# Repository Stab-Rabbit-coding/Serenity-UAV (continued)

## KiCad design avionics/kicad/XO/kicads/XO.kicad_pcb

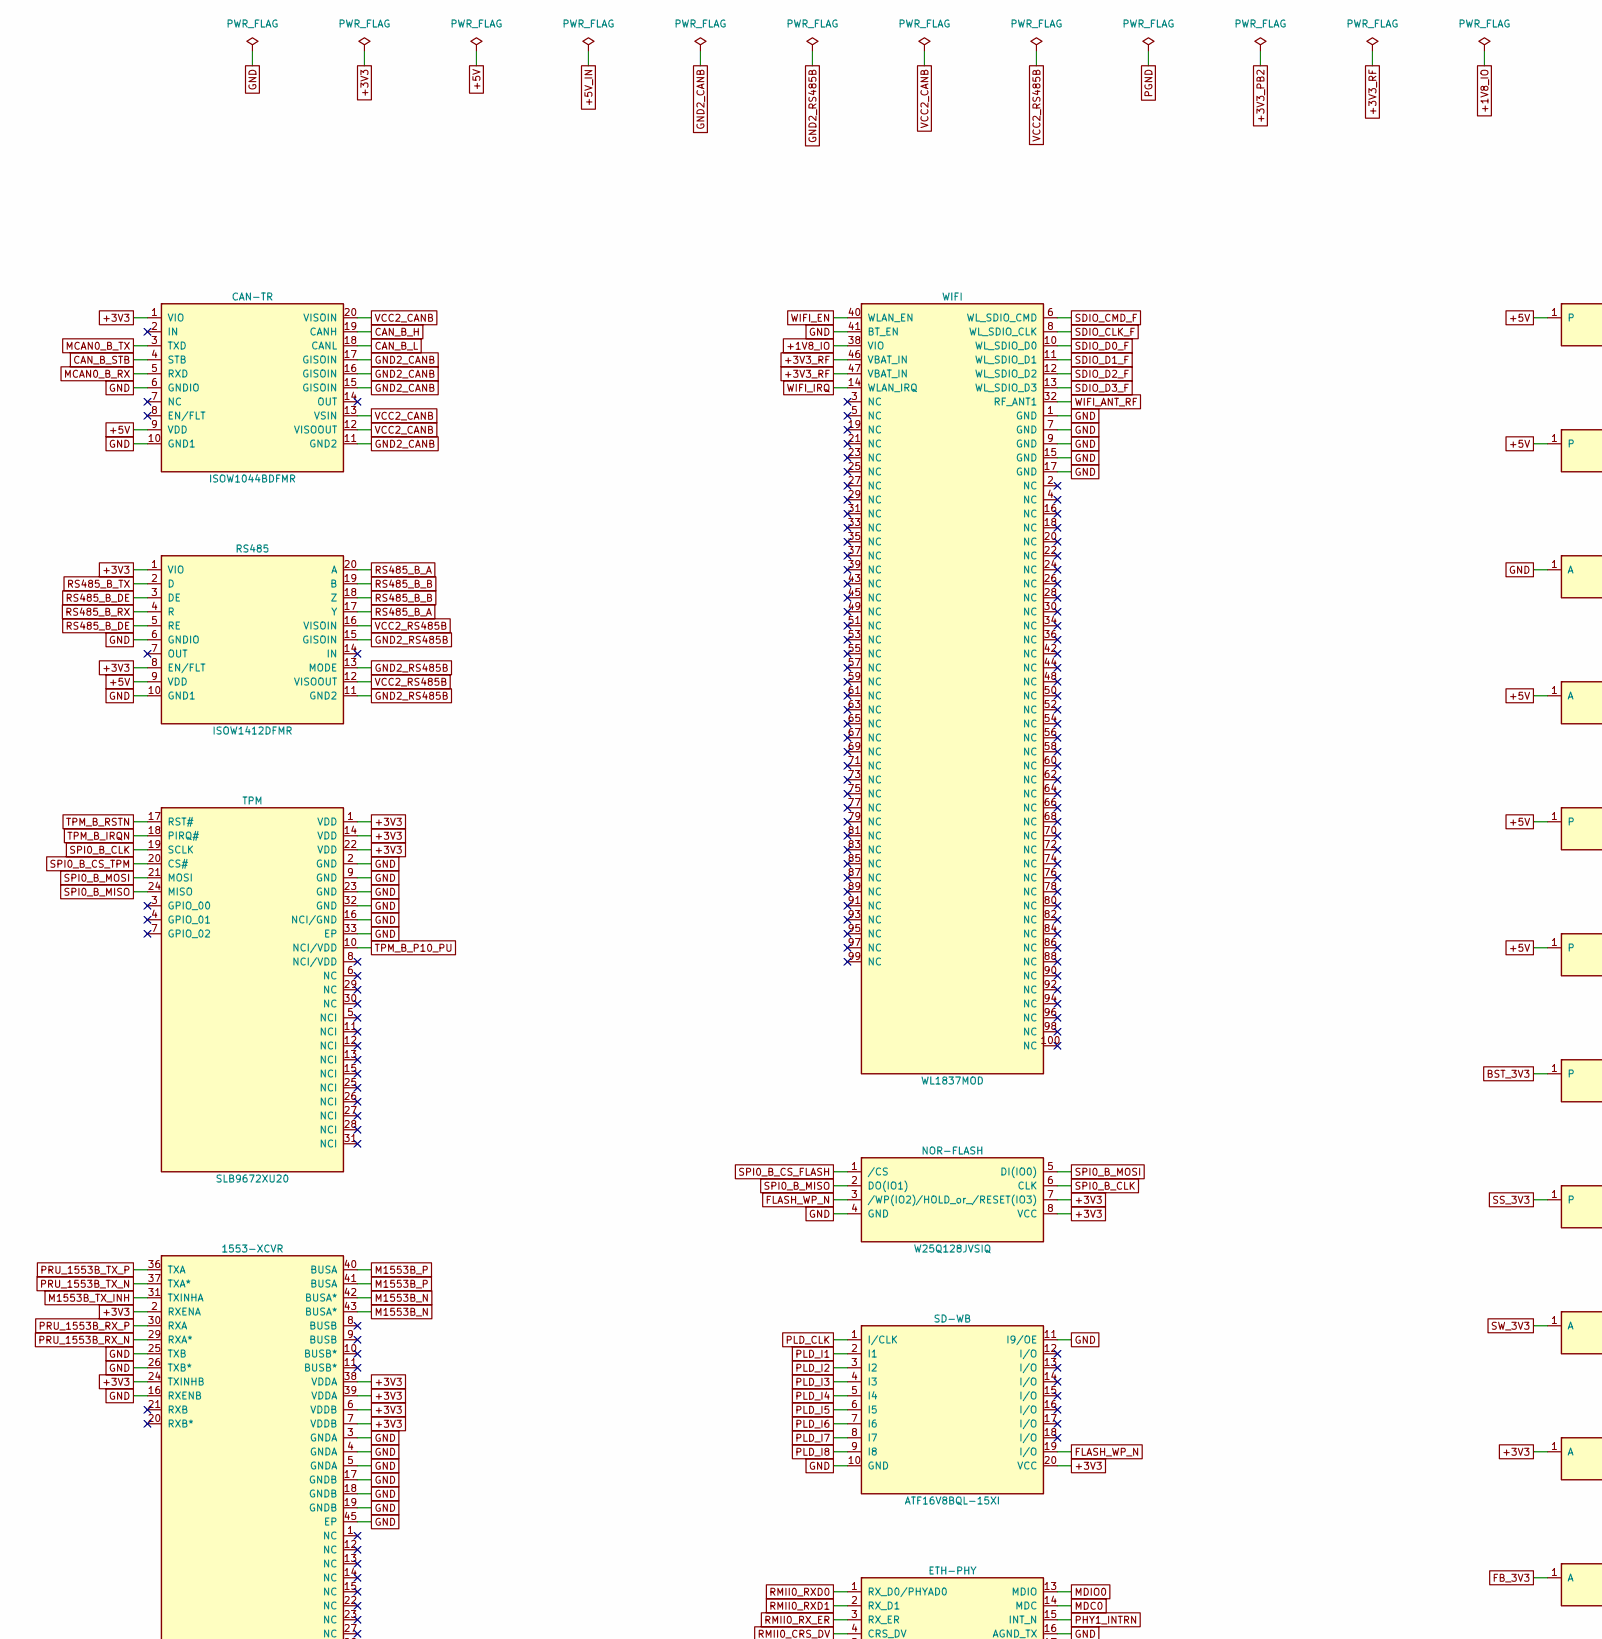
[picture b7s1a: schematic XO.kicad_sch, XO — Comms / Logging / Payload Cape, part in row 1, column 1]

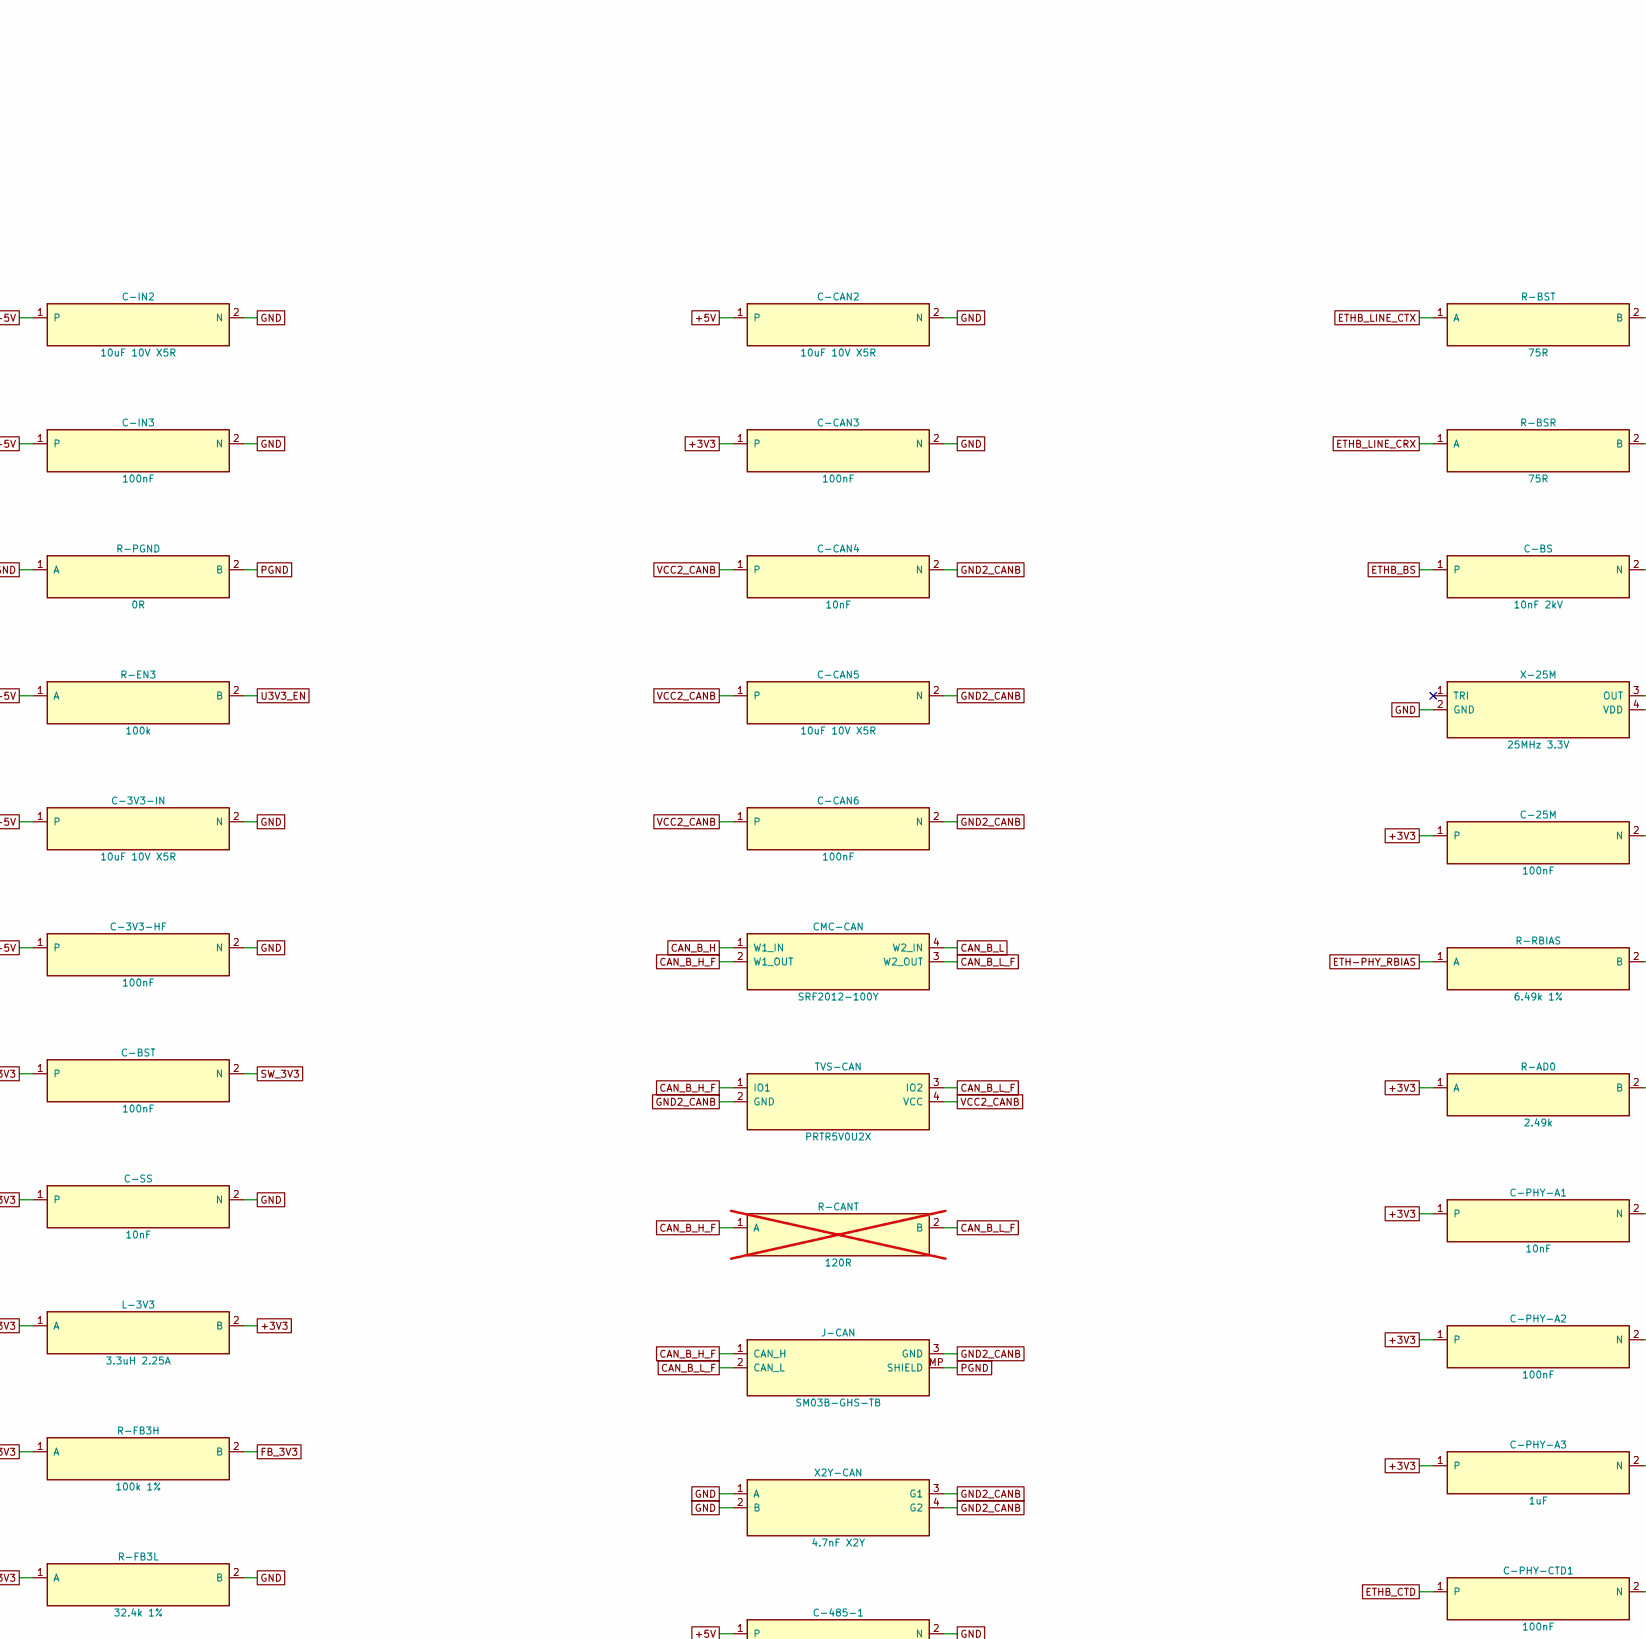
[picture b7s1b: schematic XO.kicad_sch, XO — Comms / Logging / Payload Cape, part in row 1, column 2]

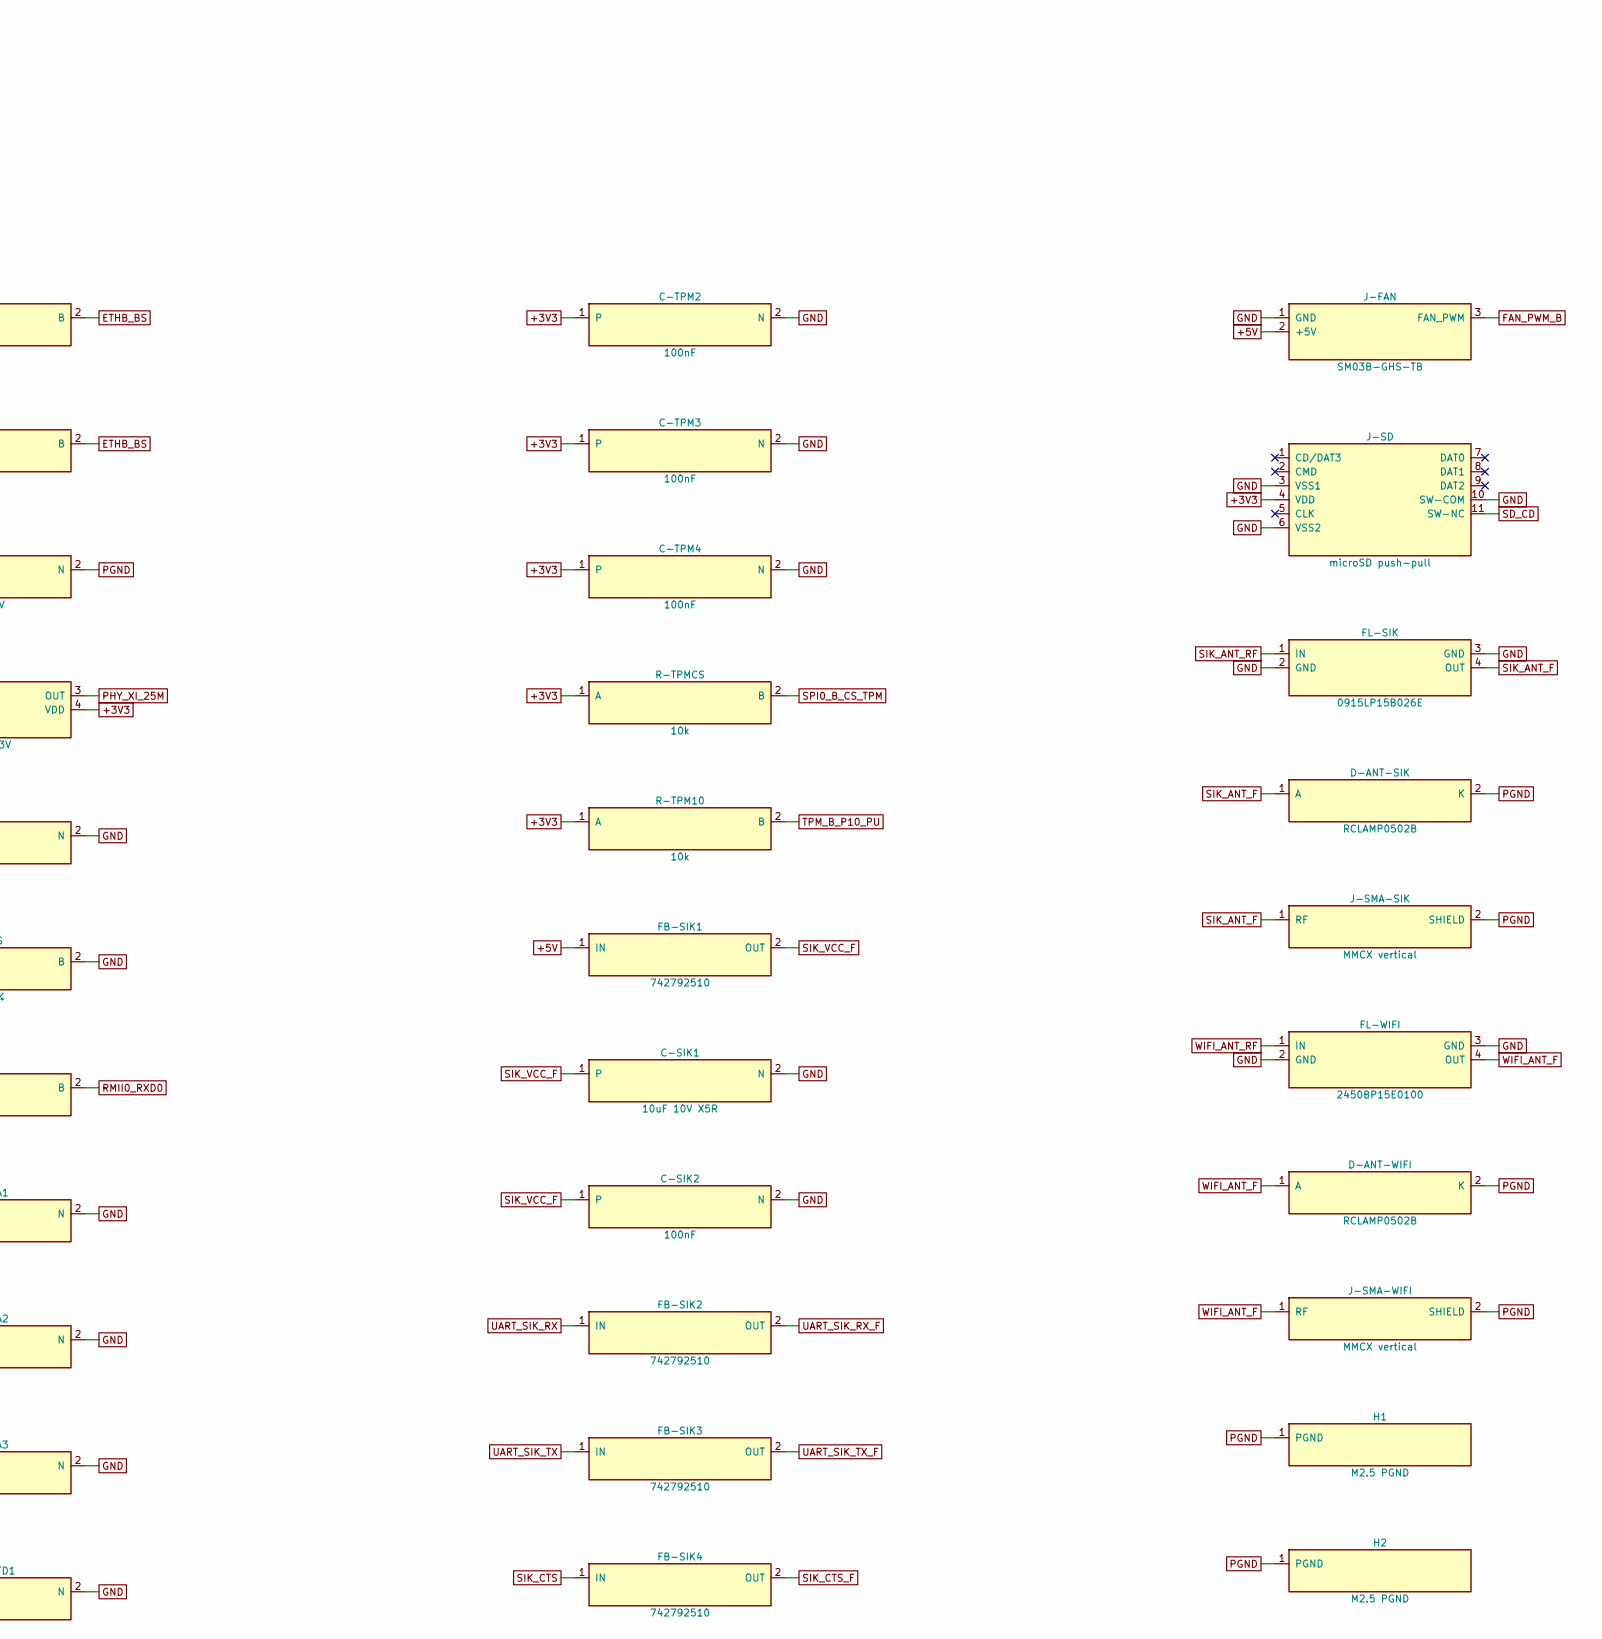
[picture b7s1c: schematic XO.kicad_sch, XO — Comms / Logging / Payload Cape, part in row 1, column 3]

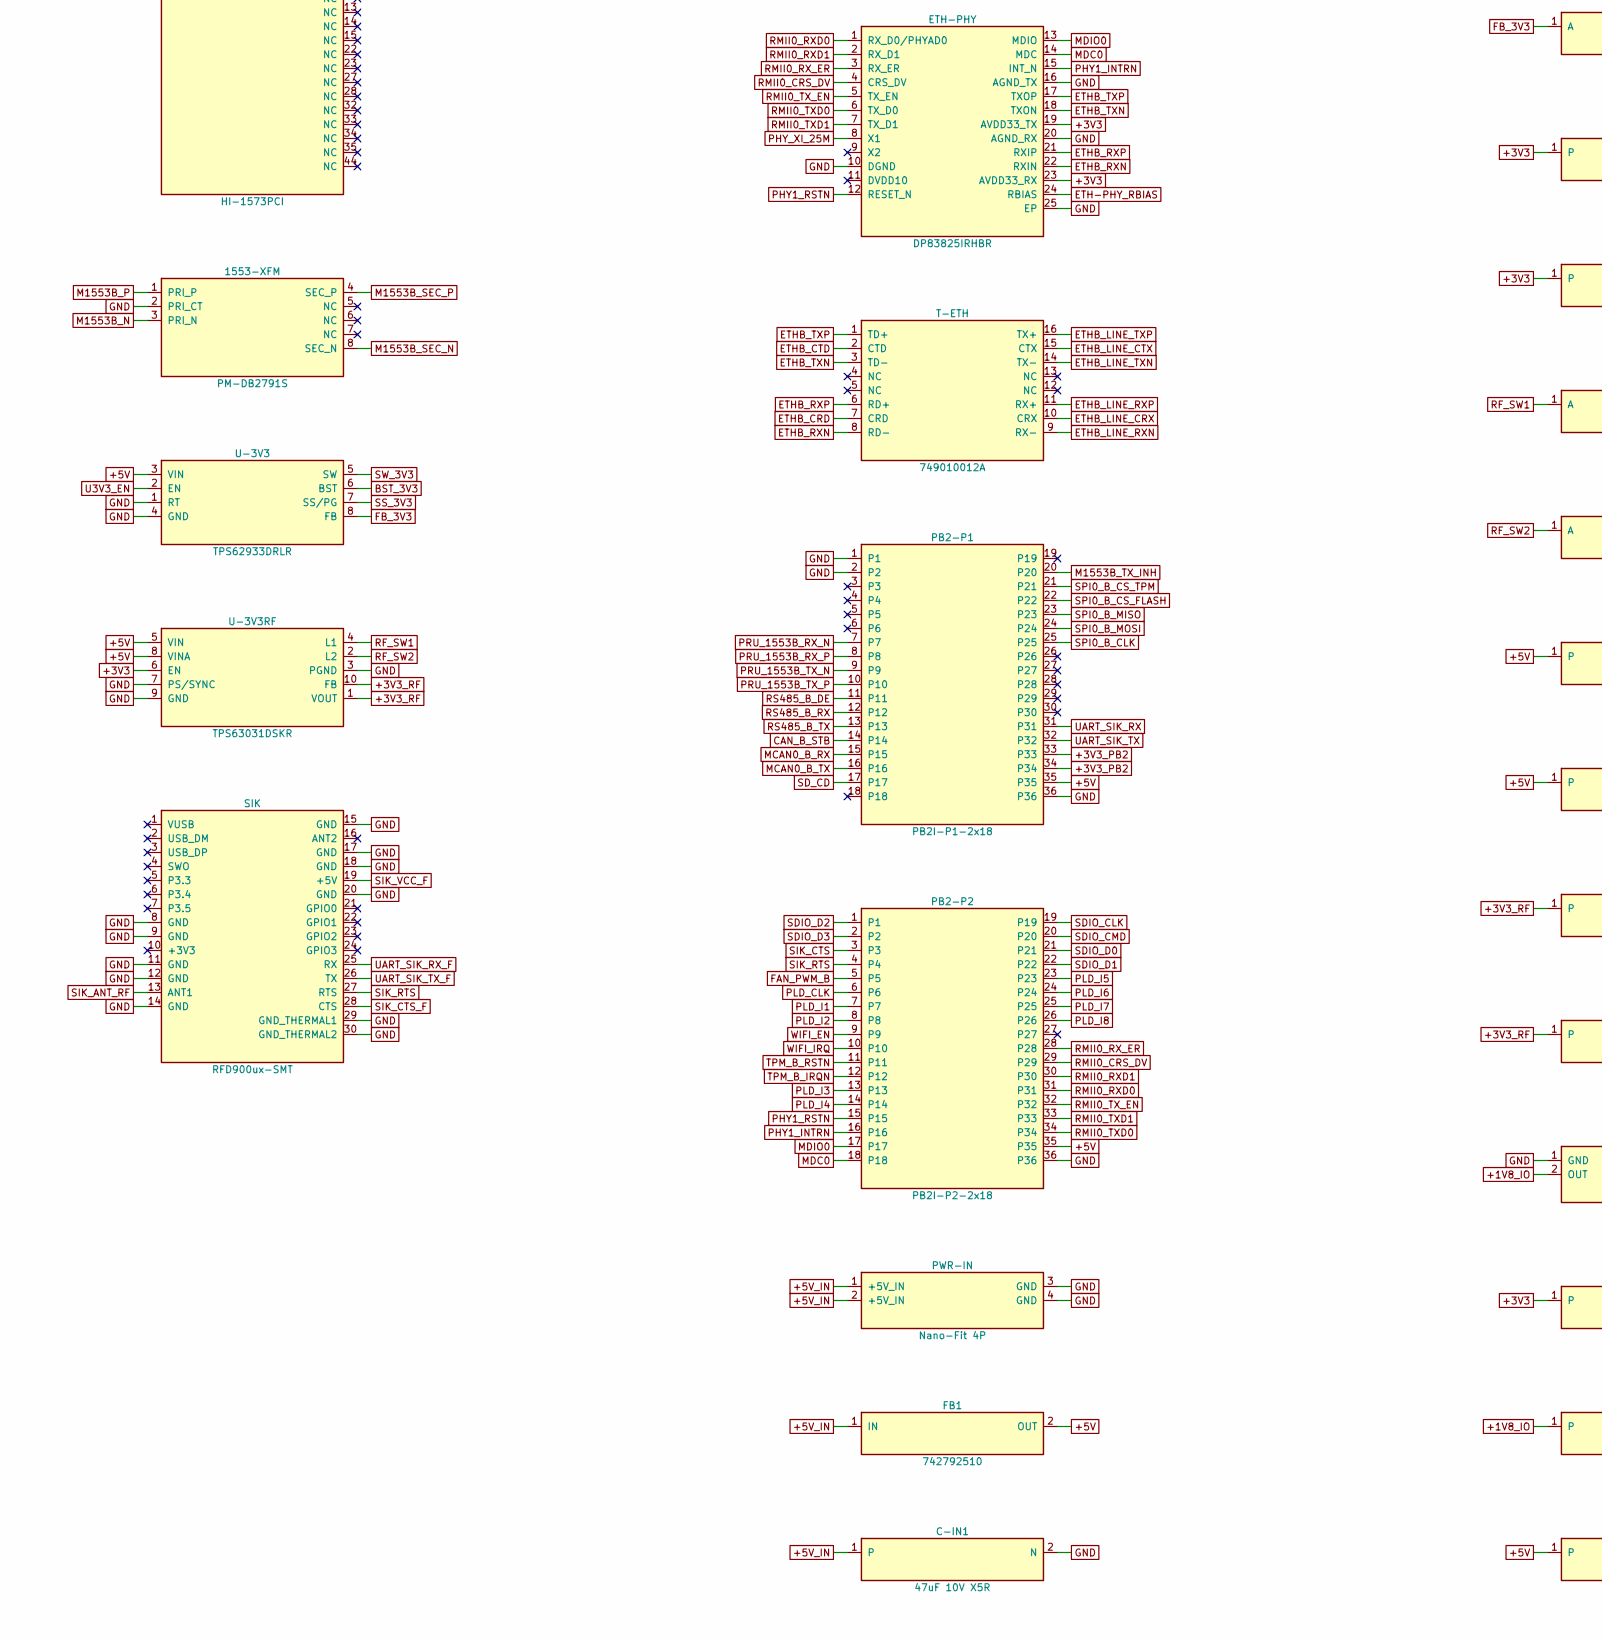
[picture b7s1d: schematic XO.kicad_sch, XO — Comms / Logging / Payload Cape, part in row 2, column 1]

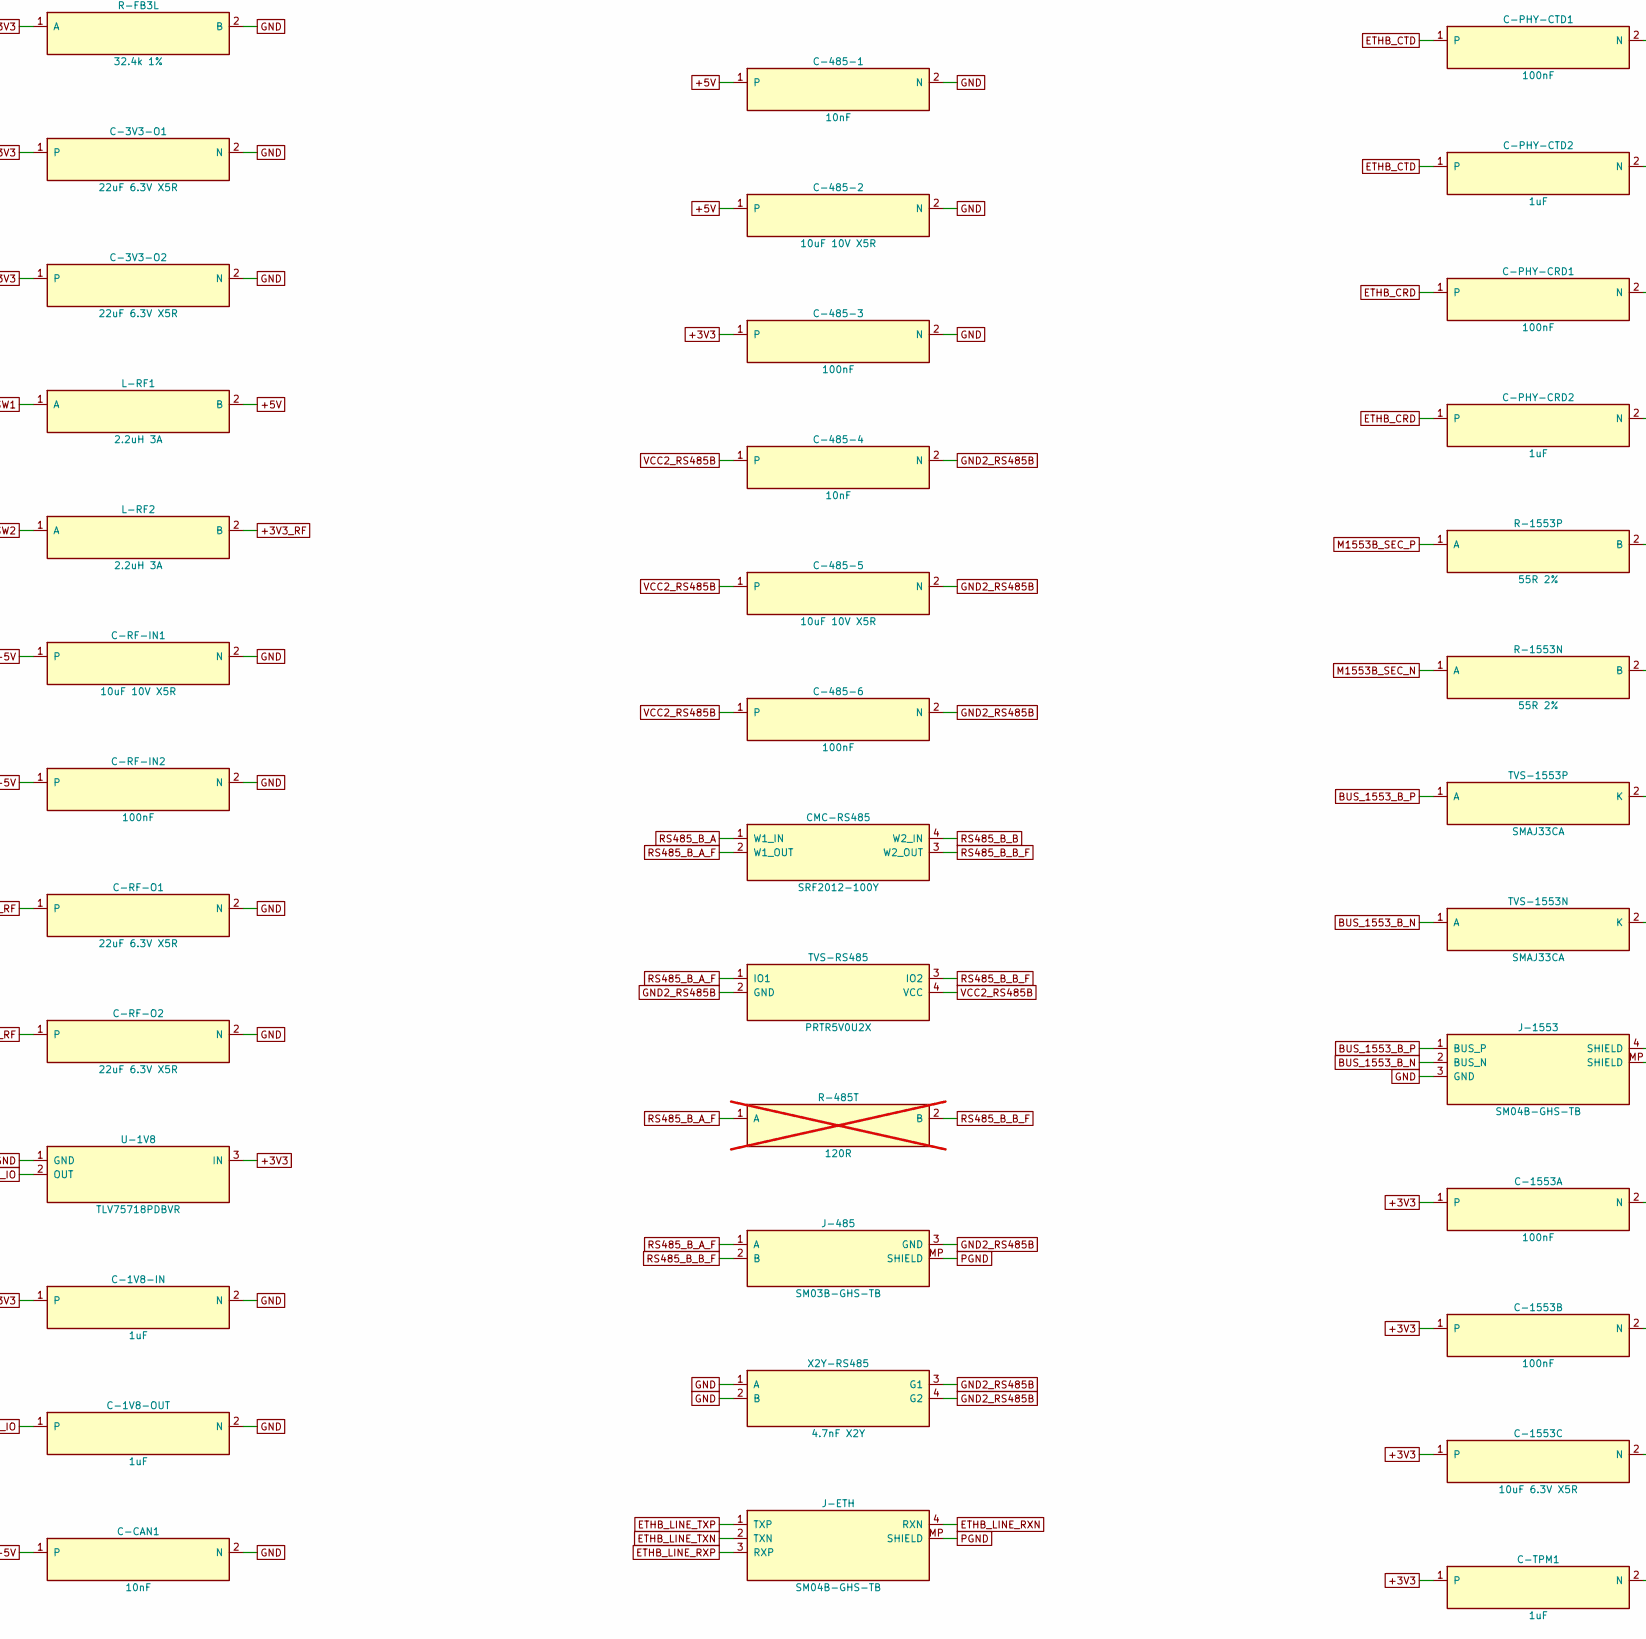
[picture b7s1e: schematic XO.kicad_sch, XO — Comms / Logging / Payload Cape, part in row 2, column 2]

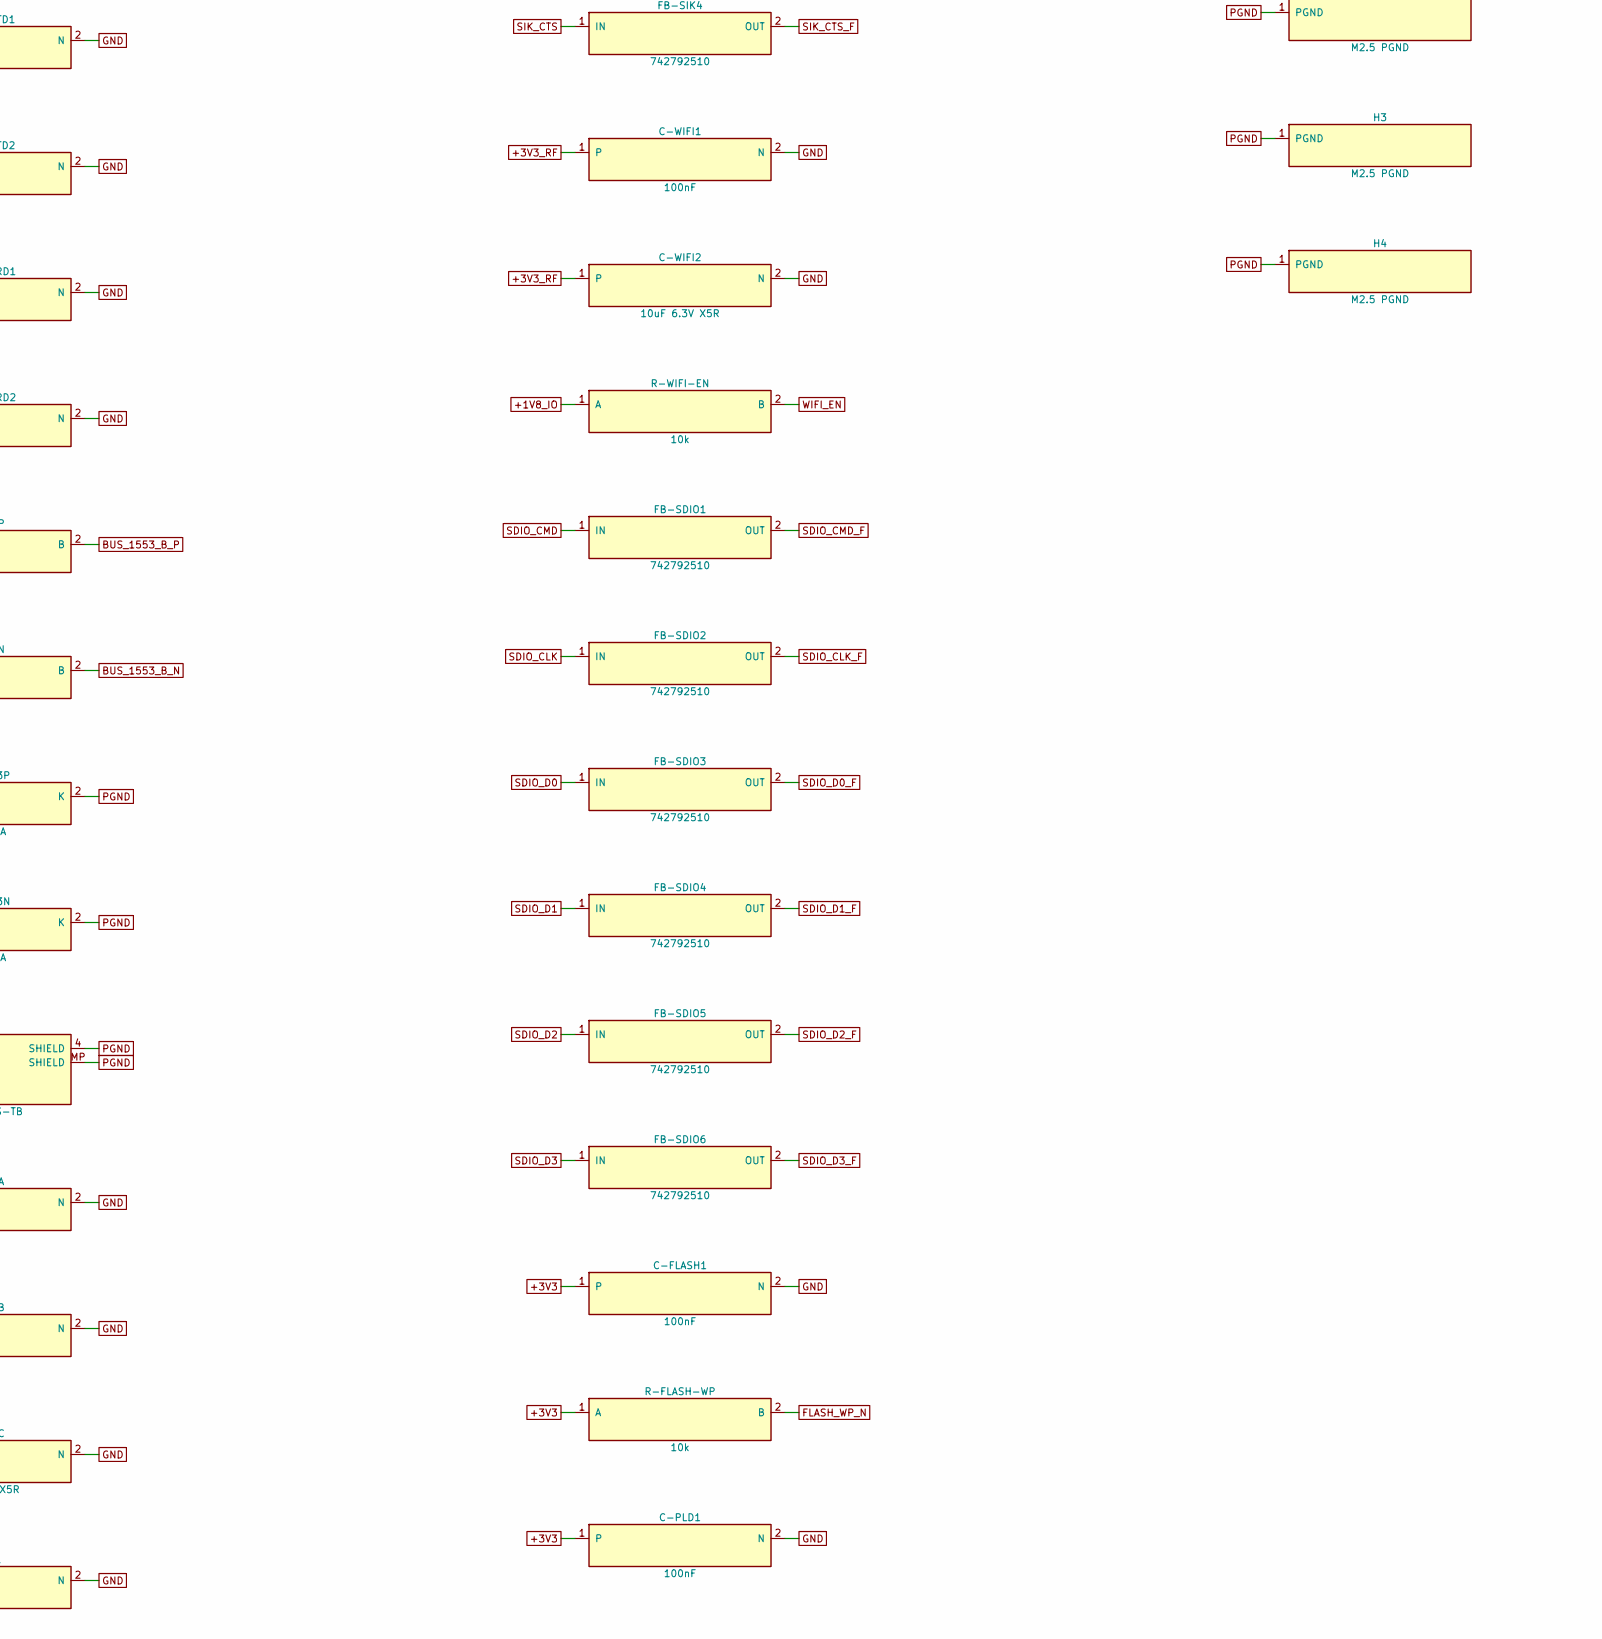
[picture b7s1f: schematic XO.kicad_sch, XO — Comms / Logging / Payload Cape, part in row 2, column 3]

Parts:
1553-XCVR: HI-1573PCI; QFN-44-1EP_7x7mm_P0.5mm_EP5.2x5.2mm; MPN HI-1573PCI
1553-XFM: PM-DB2791S; Xfmr_1553_SMD_0.40in_8pin; MPN PM-DB2791S
C-1V8-IN, C-1V8-OUT: 1uF; C_0402_1005Metric
C-3V3-HF, C-25M, C-485-3, C-485-6, C-1553A, C-1553B: 100nF; C_0402_1005Metric
C-3V3-IN, C-485-2, C-485-5: 10uF 10V X5R; C_0603_1608Metric
C-3V3-O1, C-3V3-O2: 22uF 6.3V X5R; C_0603_1608Metric
C-485-1, C-485-4: 10nF; C_0201_0603Metric
C-1553C: 10uF 6.3V X5R; C_0603_1608Metric
C-BS: 10nF 2kV; C_1808_4520Metric
C-BST: 100nF; C_0402_1005Metric
C-CAN1, C-CAN4: 10nF; C_0201_0603Metric
C-CAN2, C-CAN5: 10uF 10V X5R; C_0603_1608Metric
C-CAN3, C-CAN6: 100nF; C_0402_1005Metric
C-FLASH1: 100nF; C_0402_1005Metric
C-IN1: 47uF 10V X5R; C_1210_3225Metric
C-IN2: 10uF 10V X5R; C_0603_1608Metric
C-IN3: 100nF; C_0402_1005Metric
C-PHY-A1: 10nF; C_0201_0603Metric
C-PHY-A2: 100nF; C_0402_1005Metric
C-PHY-A3: 1uF; C_0402_1005Metric
C-PHY-CRD1: 100nF; C_0402_1005Metric
C-PHY-CRD2: 1uF; C_0402_1005Metric
C-PHY-CTD1: 100nF; C_0402_1005Metric
C-PHY-CTD2: 1uF; C_0402_1005Metric
C-PLD1: 100nF; C_0402_1005Metric
C-RF-IN1: 10uF 10V X5R; C_0603_1608Metric
C-RF-IN2: 100nF; C_0402_1005Metric
C-RF-O1, C-RF-O2: 22uF 6.3V X5R; C_0603_1608Metric
C-SIK1: 10uF 10V X5R; C_0603_1608Metric
C-SIK2: 100nF; C_0402_1005Metric
C-SS: 10nF; C_0201_0603Metric
C-TPM1: 1uF; C_0402_1005Metric
C-TPM2, C-TPM3, C-TPM4: 100nF; C_0402_1005Metric
C-WIFI1: 100nF; C_0402_1005Metric
C-WIFI2: 10uF 6.3V X5R; C_0603_1608Metric
CAN-TR: ISOW1044BDFMR; SOIC-20W_7.5x12.8mm_P1.27mm; MPN ISOW1044BDFMR
CMC-CAN: SRF2012-100Y; Bourns_SRF2012_4T; MPN SRF2012-121YA
CMC-RS485: SRF2012-100Y; Bourns_SRF2012_4T; MPN SRF2012-121YA
D-ANT-SIK: RCLAMP0502B; RCLAMP0502B_SOD882; MPN RCLAMP0502BTCL
D-ANT-WIFI: RCLAMP0502B; RCLAMP0502B_SOD882; MPN RCLAMP0502BTCL
ETH-PHY: DP83825IRHBR; Texas_RMQ0024A_WQFN-24-1EP_3x3mm_P0.4mm_EP1.9x1.9mm; MPN DP83825IRHBR
FB1: 742792510; L_1812_4532Metric; MPN 742792510
FB-SDIO1, FB-SDIO2, FB-SDIO3, FB-SDIO4, FB-SDIO5, FB-SDIO6: 742792510; L_1812_4532Metric; MPN 742792510
FB-SIK1, FB-SIK2, FB-SIK3, FB-SIK4: 742792510; L_1812_4532Metric; MPN 742792510
FL-SIK: 0915LP15B026E; Johanson_0915LP15B026E_SMD4; MPN 0915LP15B026E
FL-WIFI: 2450BP15E0100; Johanson_2450BP15E0100_SMD4; MPN 2450BP15E0100
H1, H2, H3, H4: M2.5 PGND; MountingHole_2.7mm_M2.5_PGND_Ring
J-485: SM03B-GHS-TB; JST_GH_SM03B-GHS-TB_1x03-1MP_P1.25mm_Horizontal; MPN SM03B-GHS-TB(LF)(SN)
J-1553: SM04B-GHS-TB; JST_GH_SM04B-GHS-TB_1x04-1MP_P1.25mm_Horizontal; MPN SM04B-GHS-TB(LF)(SN)
J-CAN: SM03B-GHS-TB; JST_GH_SM03B-GHS-TB_1x03-1MP_P1.25mm_Horizontal; MPN SM03B-GHS-TB(LF)(SN)
J-ETH: SM04B-GHS-TB; JST_GH_SM04B-GHS-TB_1x04-1MP_P1.25mm_Horizontal; MPN SM04B-GHS-TB(LF)(SN)
J-FAN: SM03B-GHS-TB; JST_GH_SM03B-GHS-TB_1x03-1MP_P1.25mm_Horizontal; MPN SM03B-GHS-TB(LF)(SN)
J-SD: microSD push-pull; microSD_HC_Molex_104031-0811; MPN 104031-0811
J-SMA-SIK: MMCX vertical; MMCX_Molex_73415-1471_Vertical; MPN 73415-1471
J-SMA-WIFI: MMCX vertical; MMCX_Molex_73415-1471_Vertical; MPN 73415-1471
L-3V3: 3.3uH 2.25A; L_WE-MAPI_3015; MPN 74438335033
L-RF1, L-RF2: 2.2uH 3A; L_Wuerth_MAPI-3015; MPN LPS3015-222MRC
NOR-FLASH: W25Q128JVSIQ; SOIC-8_3.9x4.9mm_P1.27mm; MPN W25Q128JVSIQ
PB2-P1: PB2I-P1-2x18; PocketBeagle2_2x18_P1_Socket
PB2-P2: PB2I-P2-2x18; PocketBeagle2_2x18_P2_Socket
PWR-IN: Nano-Fit 4P; Molex_NanoFit_1x04_Horizontal; MPN 105313-1204
R-485T: 120R; R_0402_1005Metric; not fitted
R-1553N, R-1553P: 55R 2%; R_0603_1608Metric
R-AD0: 2.49k; R_0201_0603Metric
R-BSR: 75R; R_0402_1005Metric
R-BST: 75R; R_0402_1005Metric
R-CANT: 120R; R_0402_1005Metric; not fitted
R-EN3: 100k; R_0201_0603Metric
R-FB3H: 100k 1%; R_0201_0603Metric
R-FB3L: 32.4k 1%; R_0201_0603Metric
R-FLASH-WP: 10k; R_0201_0603Metric
R-PGND: 0R; R_0805_2012Metric
R-RBIAS: 6.49k 1%; R_0201_0603Metric
R-TPM10: 10k; R_0201_0603Metric
R-TPMCS: 10k; R_0201_0603Metric
R-WIFI-EN: 10k; R_0201_0603Metric
RS485: ISOW1412DFMR; SOIC-20W_7.5x12.8mm_P1.27mm; MPN ISOW1412DFMR
SD-WB: ATF16V8BQL-15XI; TSSOP-20_4.4x6.5mm_P0.65mm; MPN ATF16V8BQL-15XI
SIK: RFD900ux-SMT; RFDesign_RFD900ux_SMT; MPN RFD900UX-SMT
T-ETH: 749010012A; Wurth_749010012A_WE-LAN; MPN 749010012A
TPM: SLB9672XU20; QFN-32-1EP_5x5mm_P0.5mm_EP3.6x3.6mm; MPN SLB9672XU20FW1611XUMA1
TVS-1553N, TVS-1553P: SMAJ33CA; D_SMA; MPN SMAJ33CA
TVS-CAN: PRTR5V0U2X; SOT-143; MPN PRTR5V0U2X,315
TVS-RS485: PRTR5V0U2X; SOT-143; MPN PRTR5V0U2X,315
U-1V8: TLV75718PDBVR; SOT-89-3; MPN TLV75718PDBVR
U-3V3: TPS62933DRLR; SOT-583-8; MPN TPS62933DRLR
U-3V3RF: TPS63031DSKR; TPS6303x_VSON-10_2p5; MPN TPS63031DSKR
WIFI: WL1837MOD; WL1837MOD_MOC_100; MPN WL1837MOD
X2Y-CAN, X2Y-RS485: 4.7nF X2Y; X2Y_0805_4T; MPN CX0805MRX7R0BB472
X-25M: 25MHz 3.3V; Oscillator_SMD_ECS_2520MV-xxx-xx-4Pin_2.5x2.0mm; MPN ECS-2520MV-250-BN-TR

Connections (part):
+1V8_IO: C-1V8-OUT.1, R-WIFI-EN.1 (A), U-1V8.2 (OUT), WIFI.38 (VIO)
+3V3: 1553-XCVR.2 (RXENA), 1553-XCVR.6 (VDDB), 1553-XCVR.7 (VDDB), 1553-XCVR.24 (TXINHB), 1553-XCVR.38 (VDDA), 1553-XCVR.39 (VDDA), C-1V8-IN.1, C-3V3-O1.1, C-3V3-O2.1, C-25M.1, C-485-3.1, C-1553A.1, C-1553B.1, C-1553C.1, C-CAN3.1, C-FLASH1.1, C-PHY-A1.1, C-PHY-A2.1, C-PHY-A3.1, C-PLD1.1, C-TPM1.1, C-TPM2.1, C-TPM3.1, C-TPM4.1, CAN-TR.1 (VIO), ETH-PHY.19 (AVDD33_TX), ETH-PHY.23 (AVDD33_RX), J-SD.4 (VDD), L-3V3.2 (B), NOR-FLASH.7 (/HOLD_or_/RESET(IO3)), NOR-FLASH.8 (VCC), R-AD0.1 (A), R-FB3H.1 (A), R-FLASH-WP.1 (A), R-TPM10.1 (A), R-TPMCS.1 (A), RS485.1 (VIO), RS485.8 (EN/FLT), SD-WB.20 (VCC), TPM.1 (VDD), TPM.14 (VDD), TPM.22 (VDD), U-1V8.3 (IN), U-3V3RF.6 (EN), X-25M.4 (VDD)
+3V3_PB2: PB2-P1.33, PB2-P1.34
+3V3_RF: C-RF-O1.1, C-RF-O2.1, C-WIFI1.1, C-WIFI2.1, L-RF2.2 (B), U-3V3RF.1 (VOUT), U-3V3RF.10 (FB), WIFI.46 (VBAT_IN), WIFI.47 (VBAT_IN)
+5V: C-3V3-HF.1, C-3V3-IN.1, C-485-1.1, C-485-2.1, C-CAN1.1, C-CAN2.1, C-IN2.1, C-IN3.1, C-RF-IN1.1, C-RF-IN2.1, CAN-TR.9 (VDD), FB1.2 (OUT), FB-SIK1.1 (IN), J-FAN.2 (+5V), L-RF1.2 (B), PB2-P1.35, PB2-P2.35, R-EN3.1 (A), RS485.9 (VDD), U-3V3.3 (VIN), U-3V3RF.5 (VIN), U-3V3RF.8 (VINA)
+5V_IN: C-IN1.1, FB1.1 (IN), PWR-IN.1 (+5V_IN), PWR-IN.2 (+5V_IN)
BST_3V3: C-BST.1, U-3V3.6 (BST)
BUS_1553_B_N: J-1553.2 (BUS_N), R-1553N.2 (B), TVS-1553N.1 (A)
BUS_1553_B_P: J-1553.1 (BUS_P), R-1553P.2 (B), TVS-1553P.1 (A)
CAN_B_H: CAN-TR.19 (CANH), CMC-CAN.1 (W1_IN)
CAN_B_H_F: CMC-CAN.2 (W1_OUT), J-CAN.1 (CAN_H), R-CANT.1 (A), TVS-CAN.1 (IO1)
CAN_B_L: CAN-TR.18 (CANL), CMC-CAN.4 (W2_IN)
CAN_B_L_F: CMC-CAN.3 (W2_OUT), J-CAN.2 (CAN_L), R-CANT.2 (B), TVS-CAN.3 (IO2)
CAN_B_STB: CAN-TR.4 (STB), PB2-P1.14
ETH-PHY_RBIAS: ETH-PHY.24 (RBIAS), R-RBIAS.1 (A)
ETHB_BS: C-BS.1, R-BSR.2 (B), R-BST.2 (B)
ETHB_CRD: C-PHY-CRD1.1, C-PHY-CRD2.1, T-ETH.7 (CRD)
ETHB_CTD: C-PHY-CTD1.1, C-PHY-CTD2.1, T-ETH.2 (CTD)
ETHB_LINE_CRX: R-BSR.1 (A), T-ETH.10 (CRX)
ETHB_LINE_CTX: R-BST.1 (A), T-ETH.15 (CTX)
ETHB_LINE_RXN: J-ETH.4 (RXN), T-ETH.9 (RX-)
ETHB_LINE_RXP: J-ETH.3 (RXP), T-ETH.11 (RX+)
ETHB_LINE_TXN: J-ETH.2 (TXN), T-ETH.14 (TX-)
ETHB_LINE_TXP: J-ETH.1 (TXP), T-ETH.16 (TX+)
ETHB_RXN: ETH-PHY.22 (RXIN), T-ETH.8 (RD-)
ETHB_RXP: ETH-PHY.21 (RXIP), T-ETH.6 (RD+)
ETHB_TXN: ETH-PHY.18 (TXON), T-ETH.3 (TD-)
ETHB_TXP: ETH-PHY.17 (TXOP), T-ETH.1 (TD+)
FAN_PWM_B: J-FAN.3 (FAN_PWM), PB2-P2.5
FB_3V3: R-FB3H.2 (B), R-FB3L.1 (A), U-3V3.8 (FB)
FLASH_WP_N: NOR-FLASH.3 (/WP(IO2)), R-FLASH-WP.2 (B), SD-WB.19 (I/O)
GND: 1553-XCVR.3 (GNDA), 1553-XCVR.4 (GNDA), 1553-XCVR.5 (GNDA), 1553-XCVR.16 (RXENB), 1553-XCVR.17 (GNDB), 1553-XCVR.18 (GNDB), 1553-XCVR.19 (GNDB), 1553-XCVR.25 (TXB), 1553-XCVR.26 (TXB*), 1553-XCVR.45 (EP), 1553-XFM.2 (PRI_CT), C-1V8-IN.2 (N), C-1V8-OUT.2 (N), C-3V3-HF.2 (N), C-3V3-IN.2 (N), C-3V3-O1.2 (N), C-3V3-O2.2 (N), C-25M.2 (N), C-485-1.2 (N), C-485-2.2 (N), C-485-3.2 (N), C-1553A.2 (N), C-1553B.2 (N), C-1553C.2 (N), C-CAN1.2 (N), C-CAN2.2 (N), C-CAN3.2 (N), C-FLASH1.2 (N), C-IN1.2 (N), C-IN2.2 (N), C-IN3.2 (N), C-PHY-A1.2 (N), C-PHY-A2.2 (N), C-PHY-A3.2 (N), C-PHY-CRD1.2 (N), C-PHY-CRD2.2 (N), C-PHY-CTD1.2 (N), C-PHY-CTD2.2 (N), C-PLD1.2 (N), C-RF-IN1.2 (N), C-RF-IN2.2 (N), C-RF-O1.2 (N), C-RF-O2.2 (N), C-SIK1.2 (N), C-SIK2.2 (N), C-SS.2 (N), C-TPM1.2 (N), C-TPM2.2 (N), C-TPM3.2 (N), C-TPM4.2 (N), C-WIFI1.2 (N), C-WIFI2.2 (N), CAN-TR.6 (GNDIO), CAN-TR.10 (GND1), ETH-PHY.10 (DGND), ETH-PHY.16 (AGND_TX), ETH-PHY.20 (AGND_RX), ETH-PHY.25 (EP), FL-SIK.2 (GND), FL-SIK.3 (GND), FL-WIFI.2 (GND), FL-WIFI.3 (GND), J-1553.3 (GND), J-FAN.1 (GND), J-SD.3 (VSS1), J-SD.6 (VSS2), J-SD.10 (SW-COM), NOR-FLASH.4 (GND), PB2-P1.1, PB2-P1.2, PB2-P1.36, PB2-P2.36, PWR-IN.3 (GND), PWR-IN.4 (GND), R-FB3L.2 (B), R-PGND.1 (A), R-RBIAS.2 (B), RS485.6 (GNDIO), RS485.10 (GND1), SD-WB.10 (GND)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
GND2_CANB: C-CAN4.2 (N), C-CAN5.2 (N), C-CAN6.2 (N), CAN-TR.11 (GND2), CAN-TR.15 (GISOIN), CAN-TR.16 (GISOIN), CAN-TR.17 (GISOIN), J-CAN.3 (GND), TVS-CAN.2 (GND), X2Y-CAN.3 (G1), X2Y-CAN.4 (G2)
GND2_RS485B: C-485-4.2 (N), C-485-5.2 (N), C-485-6.2 (N), J-485.3 (GND), RS485.11 (GND2), RS485.13 (MODE), RS485.15 (GISOIN), TVS-RS485.2 (GND), X2Y-RS485.3 (G1), X2Y-RS485.4 (G2)
M1553B_N: 1553-XCVR.42 (BUSA*), 1553-XCVR.43 (BUSA*), 1553-XFM.3 (PRI_N)
M1553B_P: 1553-XCVR.40 (BUSA), 1553-XCVR.41 (BUSA), 1553-XFM.1 (PRI_P)
M1553B_SEC_N: 1553-XFM.8 (SEC_N), R-1553N.1 (A)
M1553B_SEC_P: 1553-XFM.4 (SEC_P), R-1553P.1 (A)
M1553B_TX_INH: 1553-XCVR.31 (TXINHA), PB2-P1.20
MCAN0_B_RX: CAN-TR.5 (RXD), PB2-P1.15
MCAN0_B_TX: CAN-TR.3 (TXD), PB2-P1.16
MDC0: ETH-PHY.14 (MDC), PB2-P2.18
MDIO0: ETH-PHY.13 (MDIO), PB2-P2.17
PGND: C-BS.2 (N), D-ANT-SIK.2 (K), D-ANT-WIFI.2 (K), H1.1, H2.1, H3.1, H4.1, J-485.MP (SHIELD), J-1553.4 (SHIELD), J-1553.MP (SHIELD), J-CAN.MP (SHIELD), J-ETH.MP (SHIELD), J-SMA-SIK.2 (SHIELD), J-SMA-WIFI.2 (SHIELD), R-PGND.2 (B), TVS-1553N.2 (K), TVS-1553P.2 (K)
PHY1_INTRN: ETH-PHY.15 (INT_N), PB2-P2.16
PHY1_RSTN: ETH-PHY.12 (RESET_N), PB2-P2.15
PHY_XI_25M: ETH-PHY.8 (X1), X-25M.3 (OUT)
PLD_CLK: PB2-P2.6, SD-WB.1 (I/CLK)
PLD_I1: PB2-P2.7, SD-WB.2 (I1)
PLD_I2: PB2-P2.8, SD-WB.3 (I2)
PLD_I3: PB2-P2.13, SD-WB.4 (I3)
PLD_I4: PB2-P2.14, SD-WB.5 (I4)
PLD_I5: PB2-P2.23, SD-WB.6 (I5)
PLD_I6: PB2-P2.24, SD-WB.7 (I6)
PLD_I7: PB2-P2.25, SD-WB.8 (I7)
PLD_I8: PB2-P2.26, SD-WB.9 (I8)
PRU_1553B_RX_N: 1553-XCVR.29 (RXA*), PB2-P1.7
PRU_1553B_RX_P: 1553-XCVR.30 (RXA), PB2-P1.8
PRU_1553B_TX_N: 1553-XCVR.37 (TXA*), PB2-P1.9
PRU_1553B_TX_P: 1553-XCVR.36 (TXA), PB2-P1.10
RF_SW1: L-RF1.1 (A), U-3V3RF.4 (L1)
RF_SW2: L-RF2.1 (A), U-3V3RF.2 (L2)
RMII0_CRS_DV: ETH-PHY.4 (CRS_DV), PB2-P2.29
RMII0_RXD0: ETH-PHY.1 (RX_D0/PHYAD0), PB2-P2.31, R-AD0.2 (B)
RMII0_RXD1: ETH-PHY.2 (RX_D1), PB2-P2.30
RMII0_RX_ER: ETH-PHY.3 (RX_ER), PB2-P2.28
RMII0_TXD0: ETH-PHY.6 (TX_D0), PB2-P2.34
RMII0_TXD1: ETH-PHY.7 (TX_D1), PB2-P2.33
RMII0_TX_EN: ETH-PHY.5 (TX_EN), PB2-P2.32
RS485_B_A: CMC-RS485.1 (W1_IN), RS485.17 (Y), RS485.20 (A)
RS485_B_A_F: CMC-RS485.2 (W1_OUT), J-485.1 (A), R-485T.1 (A), TVS-RS485.1 (IO1)
RS485_B_B: CMC-RS485.4 (W2_IN), RS485.18 (Z), RS485.19 (B)
RS485_B_B_F: CMC-RS485.3 (W2_OUT), J-485.2 (B), R-485T.2 (B), TVS-RS485.3 (IO2)
RS485_B_DE: PB2-P1.11, RS485.3 (DE), RS485.5 (RE)
RS485_B_RX: PB2-P1.12, RS485.4 (R)
RS485_B_TX: PB2-P1.13, RS485.2 (D)
SDIO_CLK: FB-SDIO2.1 (IN), PB2-P2.19
SDIO_CLK_F: FB-SDIO2.2 (OUT), WIFI.8 (WL_SDIO_CLK)
SDIO_CMD: FB-SDIO1.1 (IN), PB2-P2.20
SDIO_CMD_F: FB-SDIO1.2 (OUT), WIFI.6 (WL_SDIO_CMD)
SDIO_D0: FB-SDIO3.1 (IN), PB2-P2.21
SDIO_D0_F: FB-SDIO3.2 (OUT), WIFI.10 (WL_SDIO_D0)
SDIO_D1: FB-SDIO4.1 (IN), PB2-P2.22
SDIO_D1_F: FB-SDIO4.2 (OUT), WIFI.11 (WL_SDIO_D1)
SDIO_D2: FB-SDIO5.1 (IN), PB2-P2.1
SDIO_D2_F: FB-SDIO5.2 (OUT), WIFI.12 (WL_SDIO_D2)
SDIO_D3: FB-SDIO6.1 (IN), PB2-P2.2
SDIO_D3_F: FB-SDIO6.2 (OUT), WIFI.13 (WL_SDIO_D3)
SD_CD: J-SD.11 (SW-NC), PB2-P1.17
SIK_ANT_F: D-ANT-SIK.1 (A), FL-SIK.4 (OUT), J-SMA-SIK.1 (RF)
SIK_ANT_RF: FL-SIK.1 (IN), SIK.13 (ANT1)
SIK_CTS: FB-SIK4.1 (IN), PB2-P2.3
SIK_CTS_F: FB-SIK4.2 (OUT), SIK.28 (CTS)
SIK_RTS: PB2-P2.4, SIK.27 (RTS)
SIK_VCC_F: C-SIK1.1, C-SIK2.1, FB-SIK1.2 (OUT), SIK.19 (+5V)
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
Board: 6 copper layers, 121 parts (40 on the bottom side), 116 nets, no tracks yet.
